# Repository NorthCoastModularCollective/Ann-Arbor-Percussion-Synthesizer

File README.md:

# Ann Arbor Percussion Synthesizer

A module that generates “abstract” percussion sounds and has a fairly simple interface. It won’t be intended to create “bass drums” or “snares” or “hi hats”, though it’ll probably be able to make things that approximate those sounds. It is raw, dirty, glitchy, lo-fi, and abstract. A Banksy interpretation of a Dali painting of industrial-steam-punk-Qbert. Interacting with it gives you a feeling of exploration and discovery with little emphasis on predictability and reproducibility. However, great care was taken to make the experience not feel like pure chaos and randomness. 

CAUTION: this project is still in development. There are many bugs and gaps. 

Audio Sample, [here](https://soundcloud.com/verzerren/ann-arbor-percussion-synthesizer-v-001-sound-sample)

https://github.com/NorthCoastModularCollective/Ann-Arbor-Percussion-Synthesizer/assets/6989685/e6aa8b81-97f8-49d5-8cca-bbeed19dbfc6

Hardware Overview:
- Teensy 4.1
- Teensy Audio Library
- Eurorack Trigger/Gate input

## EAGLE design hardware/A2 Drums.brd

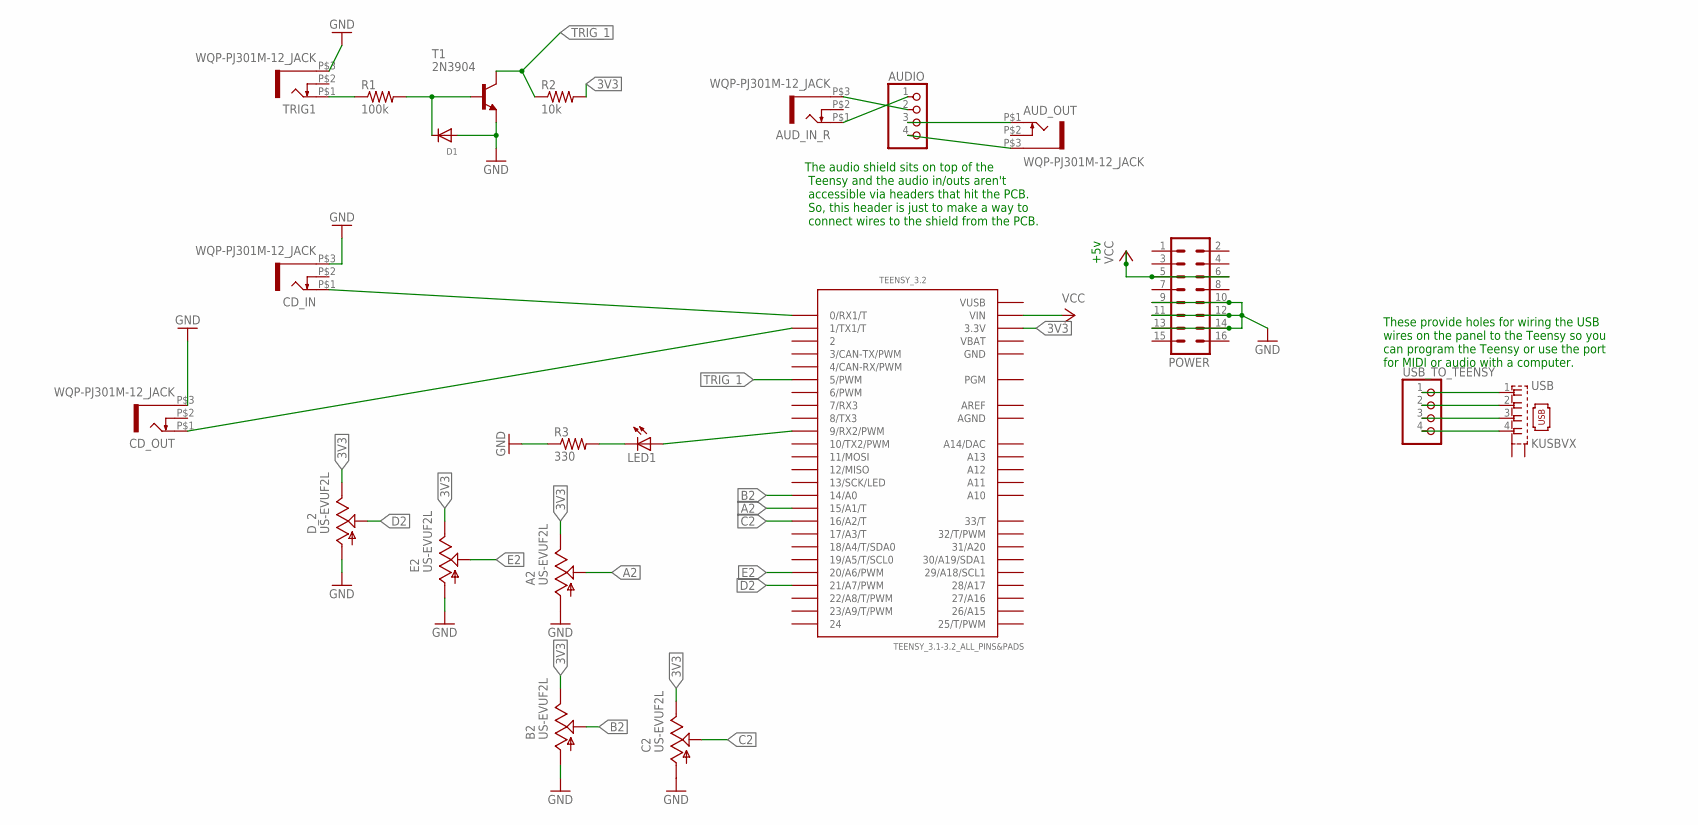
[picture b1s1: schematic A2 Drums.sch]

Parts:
A2: US-EVUF2L; EVUFXL
AUDIO: PINHD-1X4; 1X04
AUD_IN_R: WQP-PJ301M-12_JACK
AUD_OUT: WQP-PJ301M-12_JACK
B2: US-EVUF2L; EVUFXL
C2: US-EVUF2L; EVUFXL
CD_IN: WQP-PJ301M-12_JACK
CD_OUT: WQP-PJ301M-12_JACK
D1: DIODESOD-123; SOD-123
D_2: US-EVUF2L; EVUFXL
E2: US-EVUF2L; EVUFXL
LED1: LED3MM
POWER: MA08-2
R1: 100k; R0805
R2: 10k; R0805
R3: 330; R0805
T1: 2N3904; TO92
TEENSY_3.2: TEENSY_3.1-3.2_ALL_PINS&PADS; TEENSY_3.0-3.2_ALL_PINS_&_PADS
TRIG1: WQP-PJ301M-12_JACK
USB: KUSBVX
USB_TO_TEENSY: PINHD-1X4; 1X04

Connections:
3V3: A2.3 (E), B2.3 (E), C2.3 (E), D_2.3 (E), E2.3 (E), R2.2, TEENSY_3.2.3.3V, TEENSY_3.2.3.3V1 (3.3V), TEENSY_3.2.3.3V2 (3.3V)
A2: A2.2 (S), TEENSY_3.2.15/A1 (15/A1/T)
AGND: TEENSY_3.2.AGND
AREF: TEENSY_3.2.AREF
B2: B2.2 (S), TEENSY_3.2.14/A0
C2: C2.2 (S), TEENSY_3.2.16/A2 (16/A2/T)
CD_IN: CD_IN.P$1 (2), TEENSY_3.2.0 (0/RX1/T)
CD_OUT: CD_OUT.P$1 (2), TEENSY_3.2.1 (1/TX1/T)
D2: D_2.2 (S), TEENSY_3.2.21/A7 (21/A7/PWM)
E2: E2.2 (S), TEENSY_3.2.20/A6 (20/A6/PWM)
GND: A2.1 (A), B2.1 (A), C2.1 (A), CD_IN.P$3 (1), CD_OUT.P$3 (1), D1.A, D_2.1 (A), E2.1 (A), POWER.9, POWER.10, POWER.11, POWER.12, POWER.13, POWER.14, R3.1, T1.3 (E), TEENSY_3.2.GND, TEENSY_3.2.GND1 (GND), TEENSY_3.2.GND2 (GND), TRIG1.P$3 (1)
IN_R_+: AUDIO.1, AUD_IN_R.P$1 (2)
IN_R_-: AUDIO.2, AUD_IN_R.P$3 (1)
unnamed: LED1.A, TEENSY_3.2.9 (9/RX2/PWM)
unnamed: LED1.K (C), R3.2
unnamed: R1.1, TRIG1.P$1 (2)
unnamed: D1.C, R1.2, T1.2 (B)
unnamed: USB.1, USB_TO_TEENSY.1
unnamed: USB.2, USB_TO_TEENSY.2
unnamed: USB.3, USB_TO_TEENSY.3
unnamed: USB.4, USB_TO_TEENSY.4
OUT_R_+: AUDIO.3, AUD_OUT.P$1 (2)
OUT_R_-: AUDIO.4, AUD_OUT.P$3 (1)
TRIG_1: R2.1, T1.1 (C), TEENSY_3.2.5 (5/PWM)
VBAT: TEENSY_3.2.VBAT
VCC: POWER.5, POWER.6, TEENSY_3.2.VIN
VUSB: TEENSY_3.2.VUSB

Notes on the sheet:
The audio shield sits on top of the Teensy and the audio in/outs aren't accessible via headers that hit the PCB. So, this header is just to make a way to connect wires to the shield from the PCB.
These provide holes for wiring the USB wires on the panel to the Teensy so you can program the Teensy or use the port for MIDI or audio with a computer.
+5v

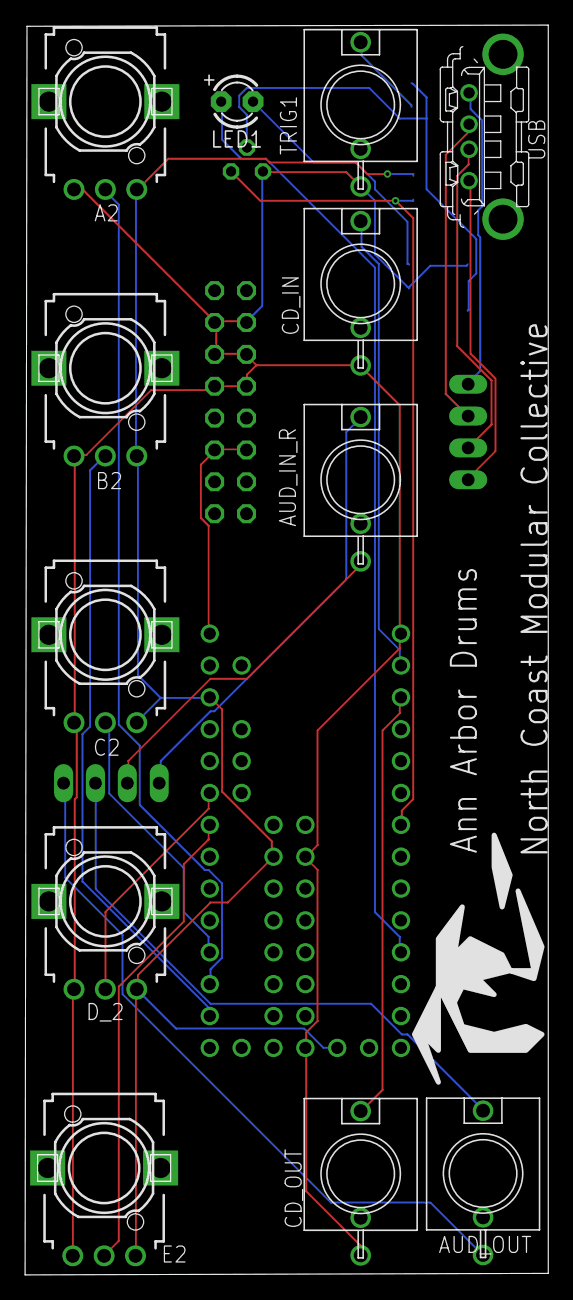
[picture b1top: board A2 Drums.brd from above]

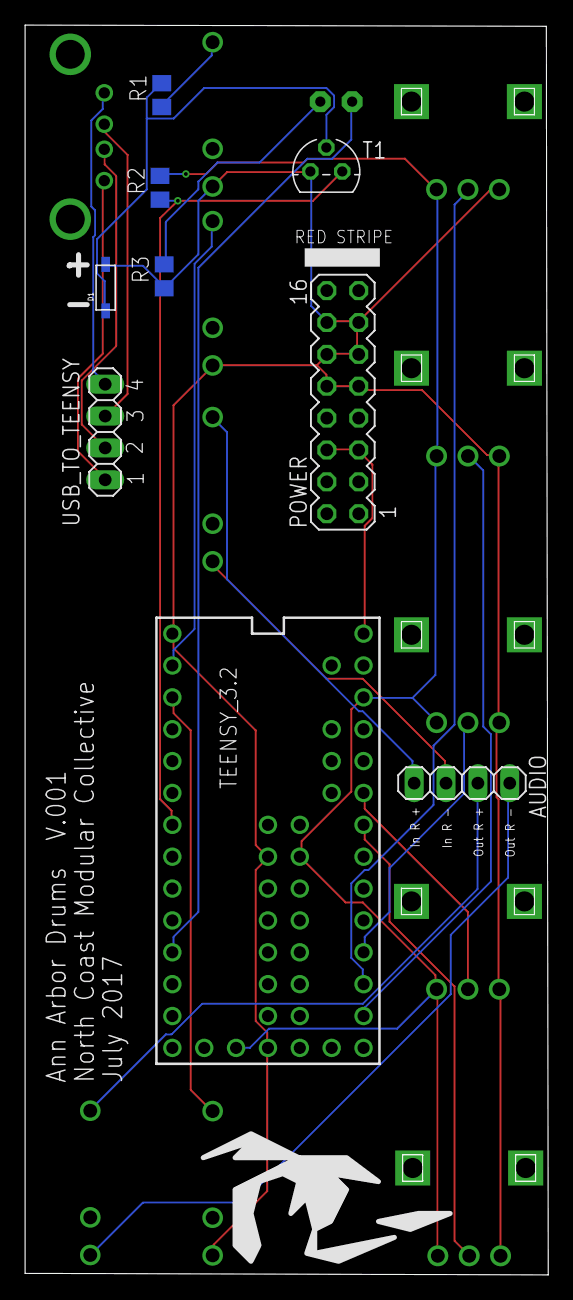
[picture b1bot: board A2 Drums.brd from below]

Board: 2 copper layers, 41.7 x 99.6 mm, 21 parts (9 on the bottom side), 23 nets.

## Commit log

2017-07-13 Unfinished Alpha Code - WORK IN PROGRESS
2017-07-13 Version .001 - WORK IN PROGRESS
    An alpha version of the board. Work in progress.
2017-07-15 Added link to audio sample
2023-11-12 Starting back over with version 1 and will rebuild up from there
    after a long hiatus, going to try and pick this one back up again. Restarting from an earlier version because some of the later versions had a lot of experiments that were me not knowing what I was d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
2023-11-12 Set up a bare basic test/validation script for Teensy and audio board to test for health
2023-11-12 Reverted back to a very old version of the code. This is super duper bad code. Don't use it yet.
2023-11-15 V2 of hardware and made a version of the software that uses the pt8211 chip for audio
2023-11-28 more small updates
2024-02-01 Updated pins for desktop hardware in code
    Set the pins in the old code to the new desktop hardware pins for the first voice.
